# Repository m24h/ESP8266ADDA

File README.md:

# ESP8266ADDA
A board that integrates ESP8266, TLV5614, and ADS1115, provides usage using arpc (Asynchronous RPC)

## Features:

* ESP8266 with WIFI for remote control.
* 4 channel single/differential 16bit ADC ADS1115/SGM58031 with rail to rail input/common voltage scope.
* 4 channel 12 bit TLV5614/MS5614.
* Using AD8532 as driver for high currents output (with protection circuits).
* 2 GPIO (IO0 and IO2), 1 ADC of ESP8266 (10bit 0-1V), 1 USART are available.
* Using Type-C USB as power supply port
* Using RPC framework for flexible remote programmable, on-site uploading python applications
* 3 demo python applications : Sampler, Calibration and CyclicVoltammetry
* Many small scripts :  call.py eval.py exec.py info.py reset.py sample.py stop.py

## Issues

* Micropython/ESP8266 sometimes stops the network response without any trace information, reset is the only way out.
* There is neither hard timer nor hard IRQ in Micropython/ESP8266, applications are somtimes limited.

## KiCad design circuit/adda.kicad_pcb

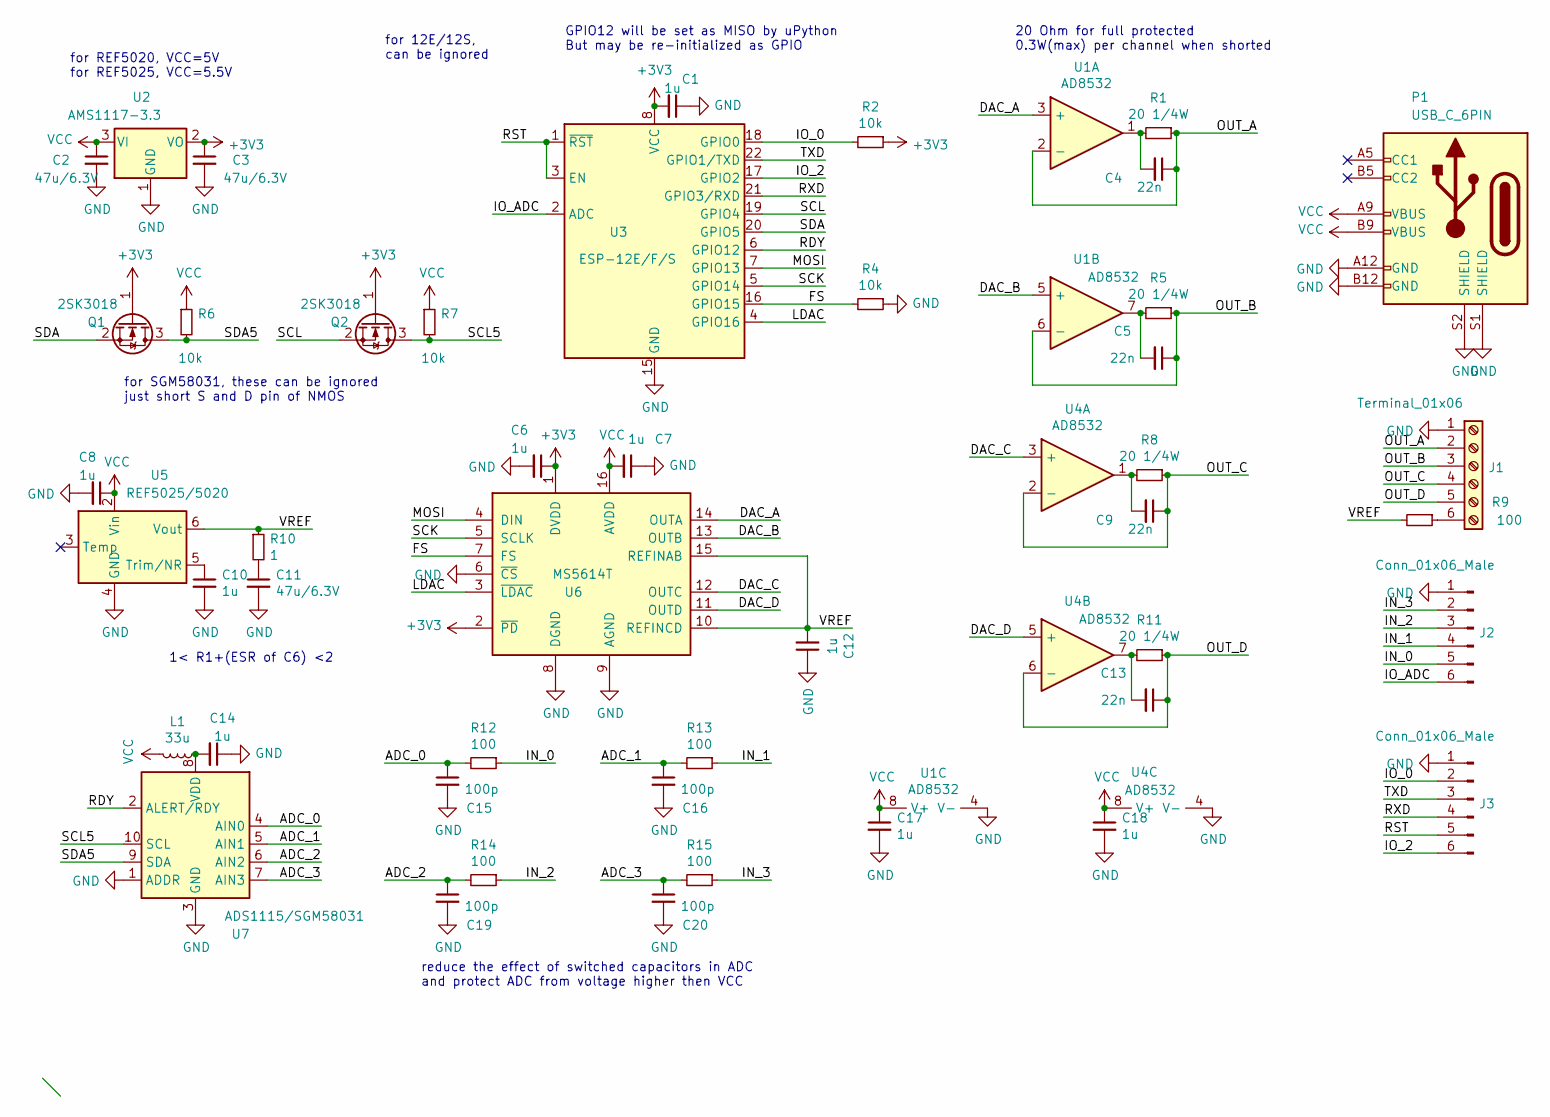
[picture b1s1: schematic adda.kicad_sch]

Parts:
C1, C6, C7, C8, C10, C12, C14, C17, C18: 1u; C_0603_1608Metric
C2, C3, C11: 47u/6.3V; C_1210_3225Metric
C4, C5, C9, C13: 22n; C_0603_1608Metric
C15, C16, C19, C20: 100p; C_0603_1608Metric
J1: Terminal_01x06; KF141V-2.54-6P
J2, J3: Conn_01x06_Male; PinHeader_1x06_P2.54mm_Vertical
L1: 33u; L_0805_2012Metric
P1: USB_C_6PIN; USB_C_6PIN_VERTICAL
Q1, Q2: 2SK3018; SOT-23
R1, R5, R8, R11: 20 1/4W; R_1206_3216Metric
R2, R4, R6, R7: 10k; R_0603_1608Metric
R9, R12, R13, R14, R15: 100; R_0603_1608Metric
R10: 1; R_0603_1608Metric
U1, U4: AD8532; SOIC-8_3.9x4.9mm_P1.27mm
U2: AMS1117-3.3; SOT-223-3_TabPin2
U3: ESP-12E/F/S; ESP-12E-NO-SD
U5: REF5025/5020; SOIC-8_3.9x4.9mm_P1.27mm
U6: MS5614T; TSSOP-16_4.4x5mm_P0.65mm
U7: ADS1115/SGM58031; TSSOP-10_3x3mm_P0.5mm

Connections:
+3V3: C1.2, C3.1, C6.1, Q1.1 (G), Q2.1 (G), R2.1, U2.2 (VO), U3.8 (VCC), U6.1 (DVDD), U6.2 (~PD)
/ADC_0: C15.1, R12.2, U7.4 (AIN0)
/ADC_1: C16.1, R13.2, U7.5 (AIN1)
/ADC_2: C19.1, R14.2, U7.6 (AIN2)
/ADC_3: C20.1, R15.2, U7.7 (AIN3)
/DAC_A: U1.3 (+), U6.14 (OUTA)
/DAC_B: U1.5 (+), U6.13 (OUTB)
/DAC_C: U4.3 (+), U6.12 (OUTC)
/DAC_D: U4.5 (+), U6.11 (OUTD)
/FS: R4.2, U3.16 (GPIO15), U6.7 (FS)
/IN_0: J2.5, R12.1
/IN_1: J2.4, R13.1
/IN_2: J2.3, R14.1
/IN_3: J2.2, R15.1
/IO_0: J3.2, R2.2, U3.18 (GPIO0)
/IO_2: J3.6, U3.17 (GPIO2)
/IO_ADC: J2.6, U3.2 (ADC)
/LDAC: U3.4 (GPIO16), U6.3 (~LDAC)
/MOSI: U3.7 (GPIO13), U6.4 (DIN)
/OUT_A: C4.1, J1.2, R1.1, U1.2 (-)
/OUT_B: C5.1, J1.3, R5.1, U1.6 (-)
/OUT_C: C9.1, J1.4, R8.1, U4.2 (-)
/OUT_D: C13.1, J1.5, R11.1, U4.6 (-)
/RDY: U3.6 (GPIO12), U7.2 (ALERT/RDY)
/RST: J3.5, U3.1 (~RST), U3.3 (EN)
/RXD: J3.4, U3.21 (GPIO3/RXD)
/SCK: U3.5 (GPIO14), U6.5 (SCLK)
/SCL: Q2.2 (S), U3.19 (GPIO4)
/SCL5: Q2.3 (D), R7.2, U7.10 (SCL)
/SDA: Q1.2 (S), U3.20 (GPIO5)
/SDA5: Q1.3 (D), R6.2, U7.9 (SDA)
/TXD: J3.3, U3.22 (GPIO1/TXD)
/VREF: C12.2, R9.2, R10.1, U5.6 (Vout), U6.10 (REFINCD), U6.15 (REFINAB)
GND: C1.1, C2.2, C3.2, C6.2, C7.1, C8.2, C10.2, C11.2, C12.1, C14.1, C15.2, C16.2, C17.2, C18.2, C19.2, C20.2, J1.1, J2.1, J3.1, P1.A12 (GND), P1.B12 (GND), P1.S1 (SHIELD), P1.S2 (SHIELD), R4.1, U1.4 (V-), U2.1 (GND), U3.15 (GND), U4.4 (V-), U5.4 (GND), U6.6 (~CS), U6.8 (DGND), U6.9 (AGND), U7.1 (ADDR), U7.3 (GND)
unnamed: C4.2, R1.2, U1.1
unnamed: C5.2, R5.2, U1.7
unnamed: C9.2, R8.2, U4.1
unnamed: C10.1, U5.5 (Trim/NR)
unnamed: C11.1, R10.2
unnamed: C13.2, R11.2, U4.7
unnamed: C14.2, L1.1, U7.8 (VDD)
unnamed: J1.6, R9.1
VCC: C2.1, C7.2, C8.1, C17.1, C18.1, L1.2, P1.A9 (VBUS), P1.B9 (VBUS), R6.1, R7.1, U1.8 (V+), U2.3 (VI), U4.8 (V+), U5.2 (Vin), U6.16 (AVDD)

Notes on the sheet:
for 12E/12S, can be ignored
20 Ohm for full protected 0.3W(max) per channel when shorted
reduce the effect of switched capacitors in ADC and protect ADC from voltage higher then VCC
1< R1+(ESR of C6) <2
for REF5020, VCC=5V for REF5025, VCC=5.5V
for SGM58031, these can be ignored just short S and D pin of NMOS
GPIO12 will be set as MISO by uPython But may be re-initialized as GPIO

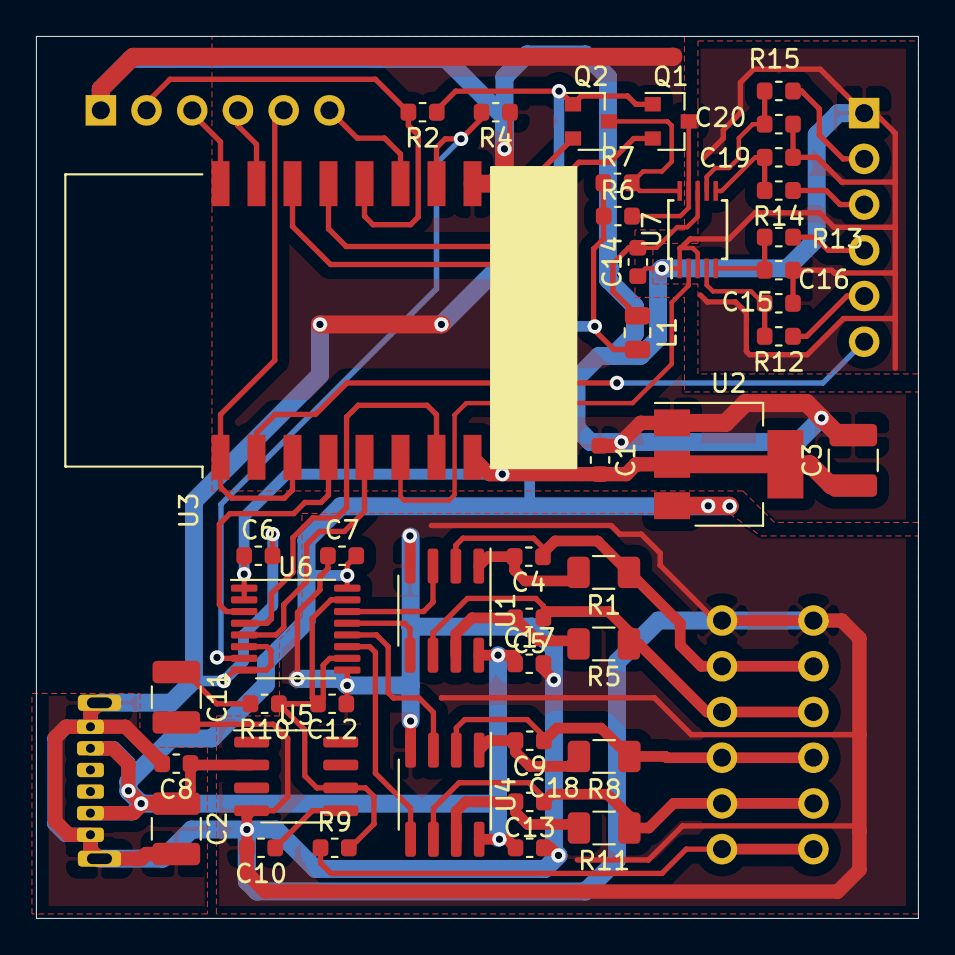
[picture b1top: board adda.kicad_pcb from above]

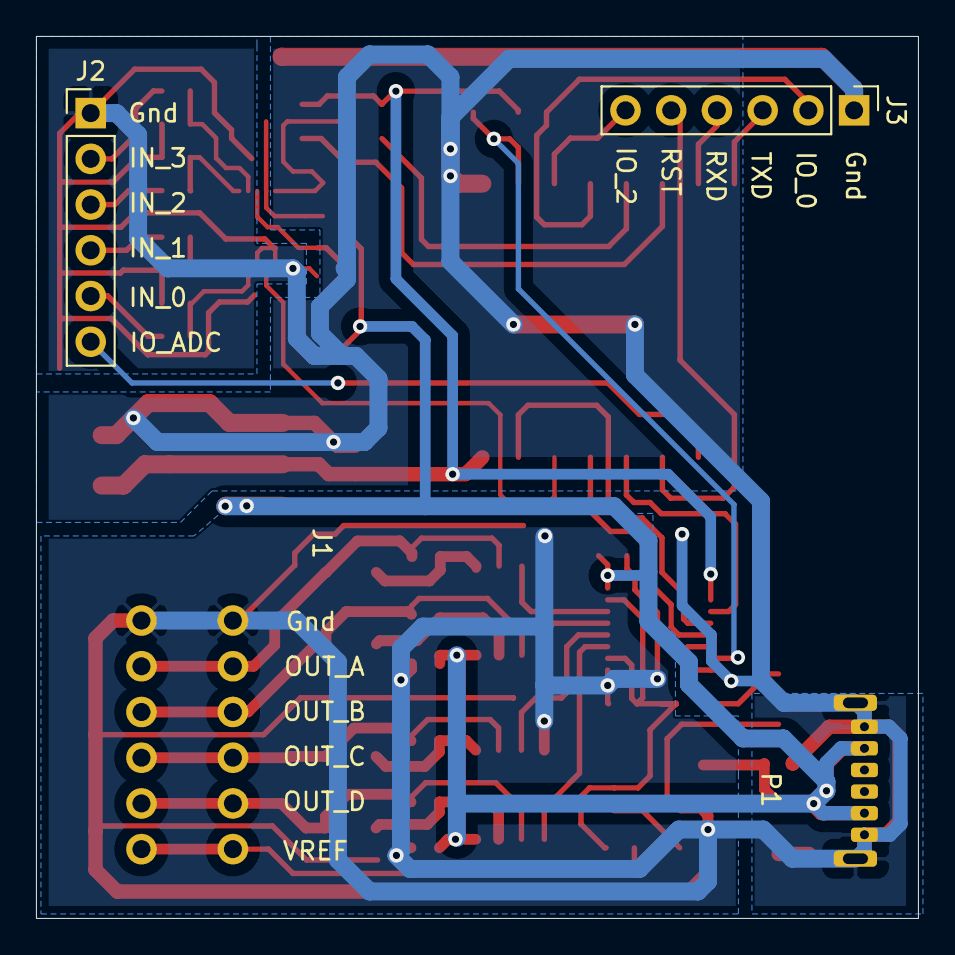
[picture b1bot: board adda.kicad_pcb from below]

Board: 2 copper layers, 49.0 x 49.0 mm, 48 parts (4 on the bottom side), 43 nets.

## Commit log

2023-03-24 Fist push Signed-off-by: m24h <jjkkxyz@hotmail.com>
2023-03-24 Update Signed-off-by: m24h <jjkkxyz@hotmail.com>
2023-03-24 Intro. is written Signed-off-by: m24h <jjkkxyz@hotmail.com>
